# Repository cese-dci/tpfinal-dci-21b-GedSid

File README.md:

## Trabajo práctico final de la asignatura DCI ##
Este repositorio contiene el trabajo práctico final para la asignatura de Diseño de Circuitos Impresos de la carrera de posgrado de FIUBA.

* Autor: JOAQUIN ULLOA
* Título corto del trabajo:  Réplica Módulo Ethernet W5100 Mini
* Descripción:  La placa tiene un regulador de tensión, por lo que puede se pueden usar tensiones de entrada de 5 V a 12 V. Los pines de señal admiten niveles de 3,3 V y 5 V. El Módulo Ethernet tiene un conector RJ-45 estándar, con un transformador de línea integrado.

## Licencia de este trabajo ##
XXXMENCIONAR ACÁ LA LICENCIAXXX (Editar este párrafo) 
Y además colcar el archivo de texto de la misma en el directorio raíz.
Para este TP se pide que la licencia sea de hardware abierto.
Ver la sección "What license should I use?": https://www.oshwa.org/faq/

## Estructura del TP FINAL ##

Se propone y se pide utilizar la siguiente estructura.

* doc: Toda la información sobre el circuito, principalmente de autoría o procesamiento propio. Por ejemplo:
  * Notas de ingeniería propias.
  * Notas de aplicación propias.
  * Estudios previos, estado del arte, resumen de las investigaciones.
  * Notas con cálculos.
  * Dibujos adicionales.
  * Fotos de los prototipos.
  * Presupuestos, cotizaciones.
* info: Toda la iformación recolectada, principalmente de terceros, como por ejemplo:
  * Hojas de datos.
  * Notas de aplicación.
  * Info de productos comerciales.
  * Info en internet.
* pcb: Archivos de diseño esquemático y pcb.

Dependiendo la magnitud del proyecto, tendremos más o menos información en estos directorios. 
Revisar los README.md en cada directorio para conocer las pautas de cada uno para este TP.

NOTA: El alumno puede y debe borrar de este archivo todo lo que considere necesario, por ejemplo las aclaraciones del docente y esta misma nota.

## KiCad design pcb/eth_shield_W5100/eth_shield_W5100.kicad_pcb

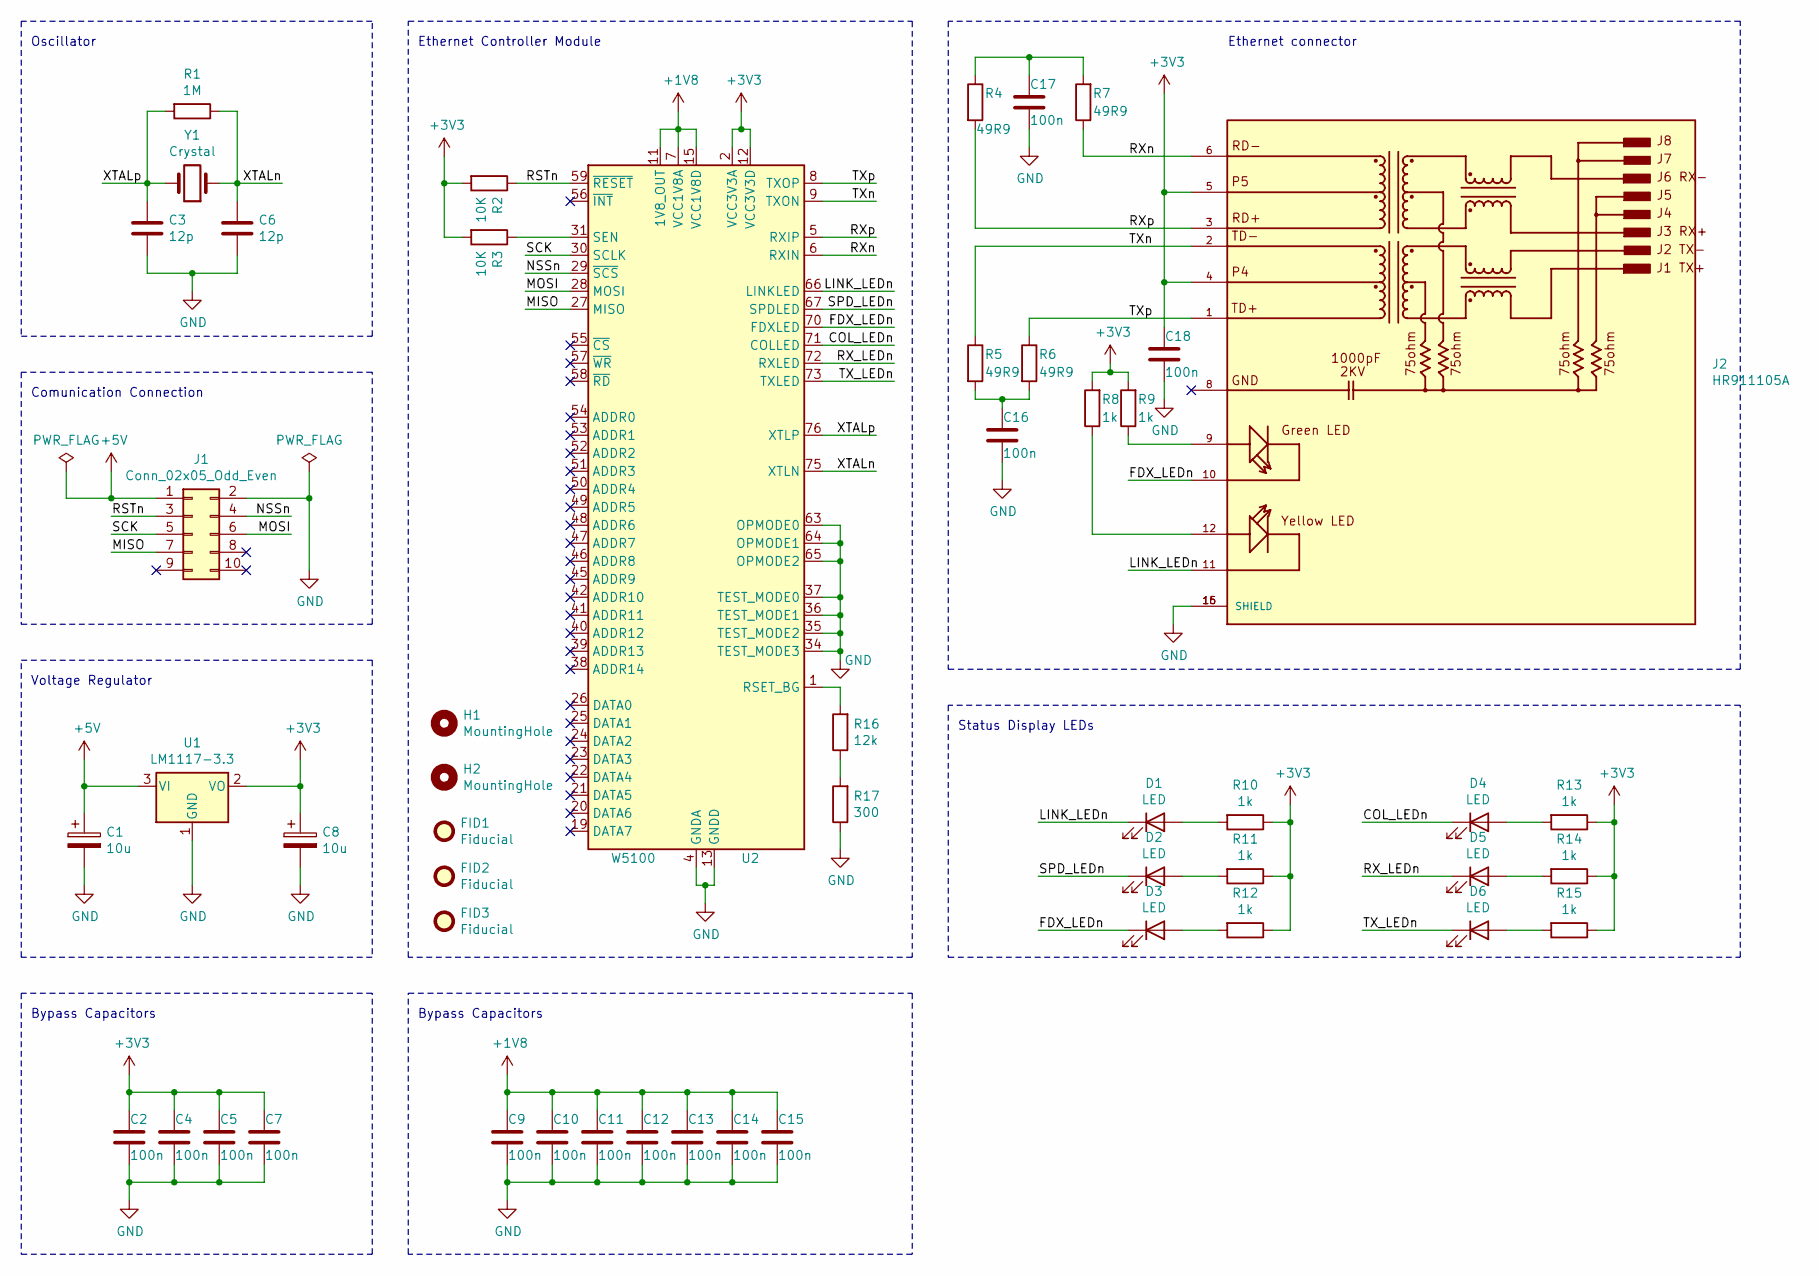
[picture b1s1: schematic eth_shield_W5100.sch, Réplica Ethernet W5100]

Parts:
C1: 10u; C_0805_2012Metric_Pad1.15x1.40mm_HandSolder
C2, C4, C5, C7, C9, C10, C11, C12, C13, C14, C15, C16, C17, C18: 100n; C_0603_1608Metric_Pad1.05x0.95mm_HandSolder
C3, C6: 12p; C_0603_1608Metric_Pad1.05x0.95mm_HandSolder
C8: 10u; C_0603_1608Metric_Pad1.05x0.95mm_HandSolder
D1, D2, D3, D4, D5, D6: LED; LED_0603_1608Metric_Pad1.05x0.95mm_HandSolder
FID1, FID2, FID3: Fiducial; Fiducial_0.75mm_Mask1.5mm
H1, H2: MountingHole; MountingHole_2.1mm
J1: Conn_02x05_Odd_Even; PinSocket_2x05_P2.54mm_Vertical
J2: HR911105A; PARTREV A
R1: 1M; R_0603_1608Metric_Pad0.98x0.95mm_HandSolder
R2, R3: 10K; R_0603_1608Metric_Pad0.98x0.95mm_HandSolder
R4, R5, R6, R7: 49R9; R_0603_1608Metric_Pad0.98x0.95mm_HandSolder
R8, R9, R10, R11, R12, R13, R14, R15: 1k; R_0603_1608Metric_Pad0.98x0.95mm_HandSolder
R16: 12k; R_0603_1608Metric_Pad0.98x0.95mm_HandSolder
R17: 300; R_0603_1608Metric_Pad0.98x0.95mm_HandSolder
U1: LM1117-3.3; SOT-223-3_TabPin2; Manufacturer PN LM1117IMPX-3.3/NOPB
U2: W5100; LQFP-80_10x10mm_P0.4mm; Manufacturer PN W5100
Y1: Crystal; Crystal_HC18-U_Vertical; Manufacturer PN ECS-200-18-4X-CKM

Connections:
+1V8: C9.1, C10.1, C11.1, C12.1, C13.1, C14.1, C15.1, U2.7 (VCC1V8A), U2.11 (1V8_OUT), U2.15 (VCC1V8D), U2.16 (VCC1V8D), U2.33 (VCC1V8D), U2.69 (VCC1V8D), U2.74 (VCC1V8A)
+3V3: C2.1, C4.1, C5.1, C7.1, C8.1, C18.1, J2.4, J2.5, R2.2, R3.2, R8.2, R9.2, R10.1, R11.1, R12.1, R13.1, R14.1, R15.1, U1.2 (VO), U2.2 (VCC3V3A), U2.12 (VCC3V3D), U2.18 (VCC3V3D), U2.44 (VCC3V3D)
+5V: C1.1, J1.1, U1.3 (VI)
/COL_LEDn: D4.1 (K), U2.71 (COLLED)
/FDX_LEDn: D3.1 (K), J2.10, U2.70 (FDXLED)
/LINK_LEDn: D1.1 (K), J2.11, U2.66 (LINKLED)
/MISO: J1.7, U2.27 (MISO)
/MOSI: J1.6, U2.28 (MOSI)
/NSSn: J1.4, U2.29 (~SCS)
/RSTn: J1.3, R2.1, U2.59 (~RESET)
/RX_LEDn: D5.1 (K), U2.72 (RXLED)
/RXn: J2.6, R7.1, U2.6 (RXIN)
/RXp: J2.3, R4.2, U2.5 (RXIP)
/SCK: J1.5, U2.30 (SCLK)
/SPD_LEDn: D2.1 (K), U2.67 (SPDLED)
/TX_LEDn: D6.1 (K), U2.73 (TXLED)
/TXn: J2.2, R5.1, U2.9 (TXON)
/TXp: J2.1, R6.1, U2.8 (TXOP)
/XTALn: C6.1, R1.1, U2.75 (XTLN), Y1.1
/XTALp: C3.1, R1.2, U2.76 (XTLP), Y1.2
GND: C1.2, C2.2, C3.2, C4.2, C5.2, C6.2, C7.2, C8.2, C9.2, C10.2, C11.2, C12.2, C13.2, C14.2, C15.2, C16.2, C17.2, C18.2, J1.2, J2.15 (SHIELD), J2.16 (SHIELD), R17.1, U1.1 (GND), U2.4 (GNDA), U2.10 (GNDA), U2.13 (GNDD), U2.14 (GNDD), U2.17 (GNDD), U2.32 (GNDD), U2.34 (TEST_MODE3), U2.35 (TEST_MODE2), U2.36 (TEST_MODE1), U2.37 (TEST_MODE0), U2.43 (GNDD), U2.63 (OPMODE0), U2.64 (OPMODE1), U2.65 (OPMODE2), U2.68 (GNDD), U2.77 (GNDA)
unnamed: C16.1, R5.2, R6.2
unnamed: C17.1, R4.1, R7.2
unnamed: D1.2 (A), R10.2
unnamed: D2.2 (A), R11.2
unnamed: D3.2 (A), R12.2
unnamed: D4.2 (A), R13.2
unnamed: D5.2 (A), R14.2
unnamed: D6.2 (A), R15.2
unnamed: J2.9, R9.1
unnamed: J2.12, R8.1
unnamed: R3.1, U2.31 (SEN)
unnamed: R16.1, R17.2
unnamed: R16.2, U2.1 (RSET_BG)

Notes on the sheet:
Bypass Capacitors
Oscillator
Ethernet Controller Module
Ethernet connector
Status Display LEDs
Voltage Regulator
Comunication Connection

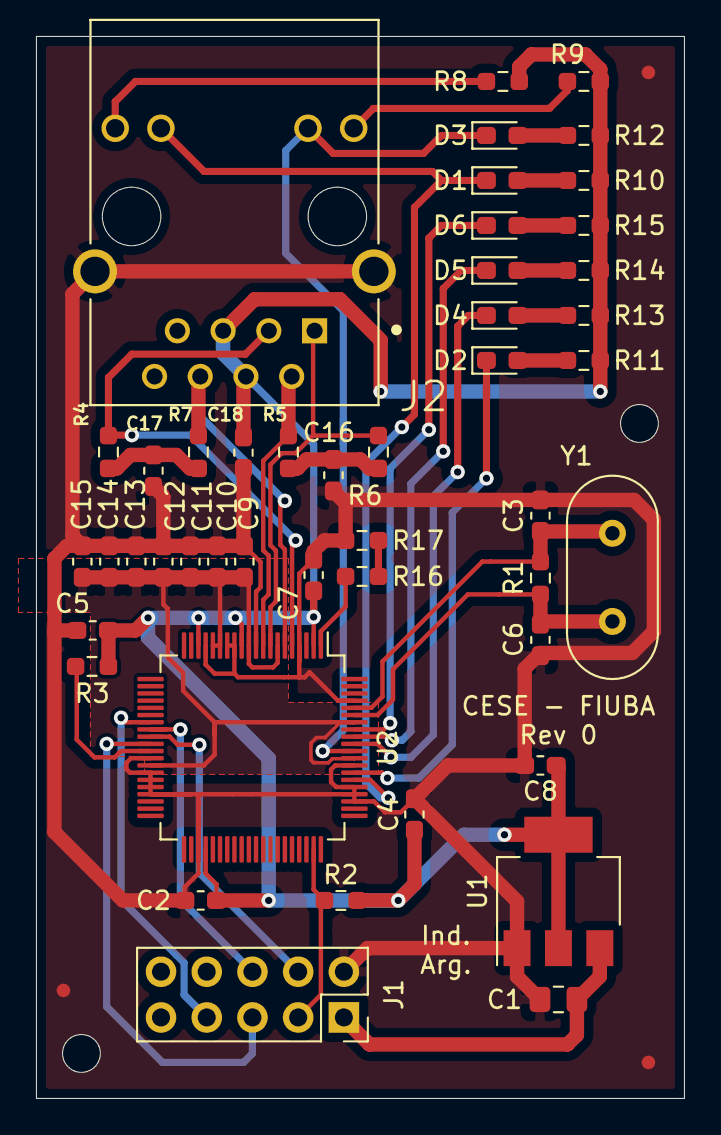
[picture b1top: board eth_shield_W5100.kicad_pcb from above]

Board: 2 copper layers, 36.0 x 59.0 mm, 51 parts (0 on the bottom side), 34 nets.

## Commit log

2021-07-25 Se agregan los archivos de la propuesta, los datasheet relevantes, las bibliotecas y el esquemático completo
2021-07-25 Se agraga la asociación de componentes y la netlist
2021-08-02 Se agregan los modelos 3D que faltan y se comienza eel routeo
2021-08-10 Se termina el routeo, se agregan comentarios y detalles
2021-08-12 Se agrega -cache.lib
2021-08-12 Se agrega agujeros y se hacen las correciones indicadas por el docente
2021-08-25 Se agregan las correciones que se hicieron para la presentación
